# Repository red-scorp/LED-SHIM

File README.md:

# LED-SHIM project

LED-SHIM (mini-HAT), RGB LED array for Raspberry Pi.

Sometimes it's nice to add some shine to your Pi.
This can be achieved with a line or matrix of RGB addressable LEDs.
Welcome to a new shiny world!

## LED-mini20-SHIM

Raspberry Pi mini 40-pin **LED-mini20-SHIM** mini-HAT.

Preview:

[Schematics in PDF format](doc/LED-mini20-SHIM.pdf)

Features:

- locked Pi headers
- data input pin selection
- 18 RGB LEDs organized in a single line
- industry standard WS2812 addressable LEDs
- small board for Pi
- can be used as SHIM (no headers) or HAT (with headers)

Pins Configuration:

|Data Pin |Option 1 |Option 2 |Option 3 |
|---------|---------|---------|---------|
|DI       |GPIO18\* |GPIO10   |GPIO21   |

\*) the pin is connected by default.

CAM files are available.
BoM and PnP files for JLCPCB are available.

## LED-mini35-SHIM

Raspberry Pi mini 40-pin **LED-mini35-SHIM** mini-HAT.

Preview:

[Schematics in PDF format](doc/LED-mini35-SHIM.pdf)

Features:

- locked Pi headers
- data input pin selection
- 12 RGB LEDs organized in a single line
- industry standard WS2812 addressable LEDs
- small board for Pi
- can be used as SHIM (no headers) or HAT (with headers)

Pins Configuration:

|Data Pin |Option 1 |Option 2 |Option 3 |
|---------|---------|---------|---------|
|DI       |GPIO18\* |GPIO10   |GPIO21   |

\*) the pin is connected by default.

CAM files are available.
BoM and PnP files for JLCPCB are available.

## LED-zero20-SHIM

Raspberry Pi zero 40-pin **LED-zero20-SHIM** mini-HAT.

Preview:

[Schematics in PDF format](doc/LED-zero20-SHIM.pdf)

Features:

- locked Pi headers
- data input pin selection
- 144 RGB LEDs organized in a matrix of 18x8
- industry standard WS2812 addressable LEDs
- separate DI and DO headers for extendability
- Pi zero board style
- can be used as SHIM (no headers) or HAT (with headers)

Pins Configuration:

|Data Pin |Option 1 |Option 2 |Option 3 |
|---------|---------|---------|---------|
|DI       |GPIO18\* |GPIO10   |GPIO21   |

\*) the pin is connected by default.

CAM files are available.
BoM and PnP files for JLCPCB are available.

## LED-zero35-SHIM

Raspberry Pi zero 40-pin **LED-zero35-SHIM** mini-HAT.

Preview:

[Schematics in PDF format](LED-zero35-SHIM.pdf)

Features:

- locked Pi headers
- data input pin selection
- 60 RGB LEDs organized in a matrix of 12x5
- industry standard WS2812 addressable LEDs
- separate DI and DO headers for extendability
- Pi zero board style
- can be used as SHIM (no headers) or HAT (with headers)

Pins Configuration:

|Data Pin |Option 1 |Option 2 |Option 3 |
|---------|---------|---------|---------|
|DI       |GPIO18\* |GPIO10   |GPIO21   |

\*) the pin is connected by default.

CAM files are available.
BoM and PnP files for JLCPCB are available.

## LED-plus20-SHIM

Raspberry Pi plus 40-pin **LED-plus20-SHIM** mini-HAT.

Preview:

[Schematics in PDF format](doc/LED-plus20-SHIM.pdf)

Features:

- locked Pi headers
- data input pin selection
- 288 RGB LEDs organized in a matrix of 18x16
- industry standard WS2812 addressable LEDs
- separate DI and DO headers for extendability
- Pi plus board style
- can be used as SHIM (no headers) or HAT (with headers)

Pins Configuration:

|Data Pin |Option 1 |Option 2 |Option 3 |
|---------|---------|---------|---------|
|DI       |GPIO18\* |GPIO10   |GPIO21   |

\*) the pin is connected by default.

CAM files are available.
BoM and PnP files for JLCPCB are available.

## LED-plus35-SHIM

Raspberry Pi plus 40-pin **LED-plus35-SHIM** mini-HAT.

Preview:

[Schematics in PDF format](doc/LED-plus35-SHIM.pdf)

Features:

- locked Pi headers
- data input pin selection
- 120 RGB LEDs organized in a matrix of 12x10
- industry standard WS2812 addressable LEDs
- separate DI and DO headers for extendability
- Pi plus board style
- can be used as SHIM (no headers) or HAT (with headers)

Pins Configuration:

|Data Pin |Option 1 |Option 2 |Option 3 |
|---------|---------|---------|---------|
|DI       |GPIO18\* |GPIO10   |GPIO21   |

\*) the pin is connected by default.

CAM files are available.
BoM and PnP files for JLCPCB are available.

## Links

- [pinout.xyz](https://pinout.xyz/) - a brilliant resource on topic of Pi's pinout and HATs.
- [raspberrypi/hats](https://github.com/raspberrypi/hats) - Pi's HAT specification.

## How to help

Your contributions as code, resources, or finances are welcome! Please contact me directly via email at andriy.golovnya@gmail.com or through my [GitHub profile](https://github.com/red-scorp).

If you'd like to make a financial contribution, you can donate via [PayPal](http://paypal.me/redscorp) or [Ko-Fi](http://ko-fi.com/redscorp). Your support is greatly appreciated.

Thanks in advance!

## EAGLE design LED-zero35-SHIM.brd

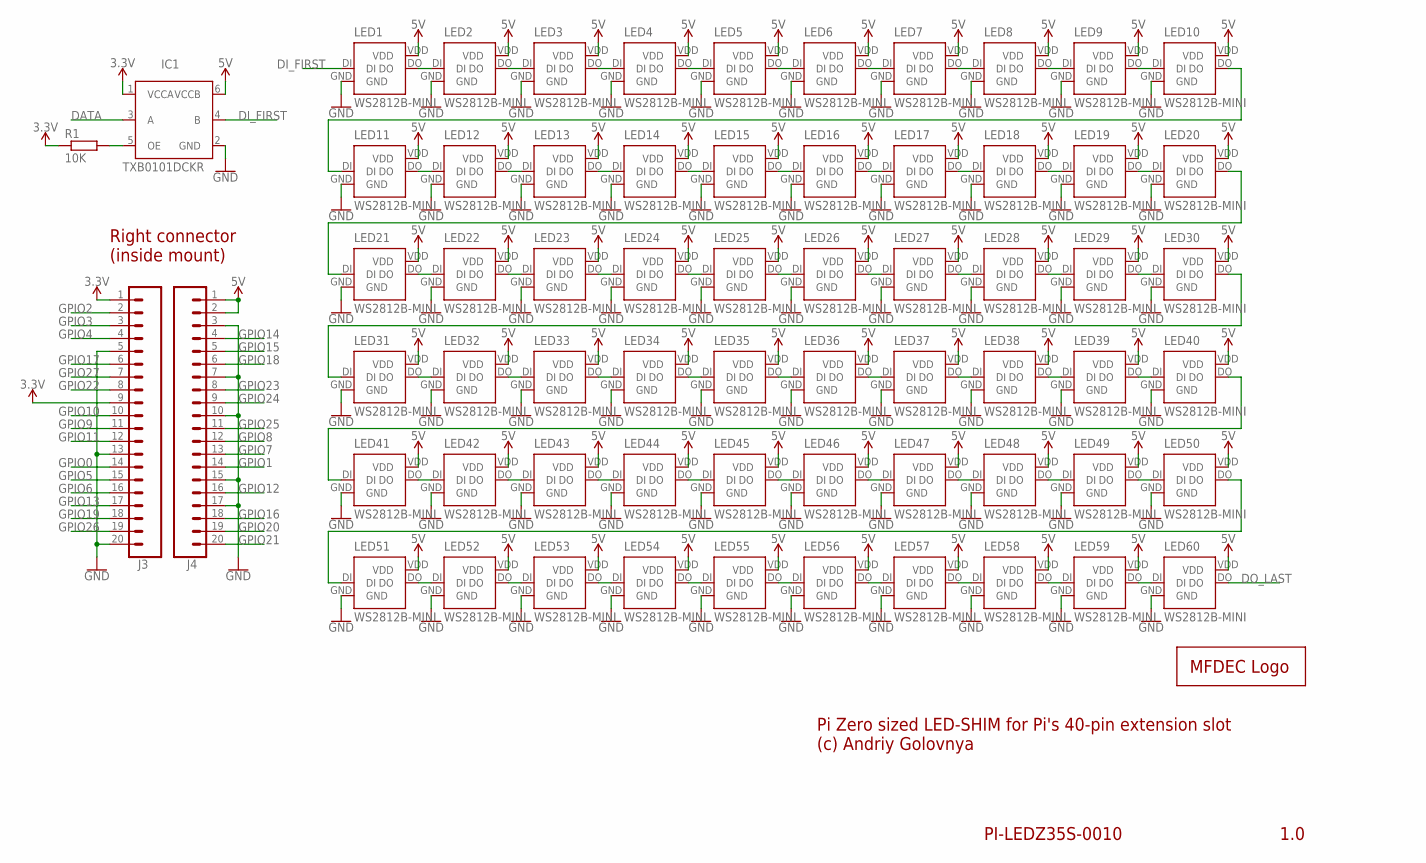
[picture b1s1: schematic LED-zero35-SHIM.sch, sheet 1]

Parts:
IC1: TXB0101DCKR; SOT65P210X110-6N
J3, J4: CONN_20LOCK; 1X20_LOCK
LED1, LED2, LED3, LED4, LED5, LED6, LED7, LED8, LED9, LED10, LED11, LED12, LED13, LED14, LED15, LED16, LED17, LED18, LED19, LED20, LED21, LED22, LED23, LED24, LED25, LED26, LED27, LED28, LED29, LED30, LED31, LED32, LED33, LED34, LED35, LED36, LED37, LED38, LED39, LED40, LED41, LED42, LED43, LED44, LED45, LED46, LED47, LED48, LED49, LED50, LED51, LED52, LED53, LED54, LED55, LED56, LED57, LED58, LED59, LED60: WS2812B-MINI; WS2812X-MINI
LOGO1: MFDECLOGO_L_30MM; MFDEC_L_30MM
R1: 10K; R0402

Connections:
3.3V: IC1.1 (VCCA), J3.1, J3.9, R1.1
5V: IC1.6 (VCCB), J4.1, J4.2, LED1.VDD, LED2.VDD, LED3.VDD, LED4.VDD, LED5.VDD, LED6.VDD, LED7.VDD, LED8.VDD, LED9.VDD, LED10.VDD, LED11.VDD, LED12.VDD, LED13.VDD, LED14.VDD, LED15.VDD, LED16.VDD, LED17.VDD, LED18.VDD, LED19.VDD, LED20.VDD, LED21.VDD, LED22.VDD, LED23.VDD, LED24.VDD, LED25.VDD, LED26.VDD, LED27.VDD, LED28.VDD, LED29.VDD, LED30.VDD, LED31.VDD, LED32.VDD, LED33.VDD, LED34.VDD, LED35.VDD, LED36.VDD, LED37.VDD, LED38.VDD, LED39.VDD, LED40.VDD, LED41.VDD, LED42.VDD, LED43.VDD, LED44.VDD, LED45.VDD, LED46.VDD, LED47.VDD, LED48.VDD, LED49.VDD, LED50.VDD, LED51.VDD, LED52.VDD, LED53.VDD, LED54.VDD, LED55.VDD, LED56.VDD, LED57.VDD, LED58.VDD, LED59.VDD, LED60.VDD; also elsewhere on the board
DATA: IC1.3 (A); also elsewhere on the board
DI_FIRST: IC1.4 (B), LED1.DI; also elsewhere on the board
DO_LAST: LED60.DO; also elsewhere on the board
GND: IC1.2 (GND), J3.5, J3.13, J3.20, J4.3, J4.7, J4.10, J4.15, J4.17, LED1.GND, LED2.GND, LED3.GND, LED4.GND, LED5.GND, LED6.GND, LED7.GND, LED8.GND, LED9.GND, LED10.GND, LED11.GND, LED12.GND, LED13.GND, LED14.GND, LED15.GND, LED16.GND, LED17.GND, LED18.GND, LED19.GND, LED20.GND, LED21.GND, LED22.GND, LED23.GND, LED24.GND, LED25.GND, LED26.GND, LED27.GND, LED28.GND, LED29.GND, LED30.GND, LED31.GND, LED32.GND, LED33.GND, LED34.GND, LED35.GND, LED36.GND, LED37.GND, LED38.GND, LED39.GND, LED40.GND, LED41.GND, LED42.GND, LED43.GND, LED44.GND, LED45.GND, LED46.GND, LED47.GND, LED48.GND, LED49.GND, LED50.GND, LED51.GND, LED52.GND, LED53.GND, LED54.GND, LED55.GND, LED56.GND, LED57.GND, LED58.GND, LED59.GND, LED60.GND; also elsewhere on the board
GPIO0: J3.14
GPIO1: J4.14
GPIO2: J3.2
GPIO3: J3.3
GPIO4: J3.4
GPIO5: J3.15
GPIO6: J3.16
GPIO7: J4.13
GPIO8: J4.12
GPIO9: J3.11
GPIO10: J3.10; also elsewhere on the board
GPIO11: J3.12
GPIO12: J4.16
GPIO13: J3.17
GPIO14: J4.4
GPIO15: J4.5
GPIO16: J4.18
GPIO17: J3.6
GPIO18: J4.6; also elsewhere on the board
GPIO19: J3.18
GPIO20: J4.19
GPIO21: J4.20; also elsewhere on the board
GPIO22: J3.8
GPIO23: J4.8
GPIO24: J4.9
GPIO25: J4.11
GPIO26: J3.19
GPIO27: J3.7
unnamed: LED1.DO, LED2.DI
unnamed: LED2.DO, LED3.DI
unnamed: LED3.DO, LED4.DI
unnamed: LED4.DO, LED5.DI
unnamed: LED5.DO, LED6.DI
unnamed: LED6.DO, LED7.DI
unnamed: LED7.DO, LED8.DI
unnamed: LED8.DO, LED9.DI
unnamed: LED9.DO, LED10.DI
unnamed: LED10.DO, LED11.DI
unnamed: LED11.DO, LED12.DI
unnamed: LED12.DO, LED13.DI
unnamed: LED13.DO, LED14.DI
unnamed: LED14.DO, LED15.DI
unnamed: LED15.DO, LED16.DI
unnamed: LED16.DO, LED17.DI
unnamed: LED17.DO, LED18.DI
unnamed: LED18.DO, LED19.DI
unnamed: LED19.DO, LED20.DI
unnamed: LED20.DO, LED21.DI
unnamed: LED21.DO, LED22.DI
unnamed: LED22.DO, LED23.DI
unnamed: LED23.DO, LED24.DI
unnamed: LED24.DO, LED25.DI
unnamed: LED25.DO, LED26.DI
unnamed: LED26.DO, LED27.DI
unnamed: LED27.DO, LED28.DI
unnamed: LED28.DO, LED29.DI
unnamed: LED29.DO, LED30.DI
unnamed: LED30.DO, LED31.DI
unnamed: LED41.DO, LED42.DI
unnamed: LED31.DO, LED32.DI
unnamed: LED32.DO, LED33.DI
unnamed: LED33.DO, LED34.DI
unnamed: LED34.DO, LED35.DI
unnamed: LED35.DO, LED36.DI
unnamed: LED36.DO, LED37.DI
unnamed: LED37.DO, LED38.DI
unnamed: LED38.DO, LED39.DI
unnamed: LED39.DO, LED40.DI
unnamed: LED40.DO, LED41.DI
unnamed: LED42.DO, LED43.DI
unnamed: LED43.DO, LED44.DI
unnamed: LED44.DO, LED45.DI
unnamed: LED45.DO, LED46.DI
unnamed: LED46.DO, LED47.DI
unnamed: LED47.DO, LED48.DI
unnamed: LED48.DO, LED49.DI
unnamed: LED49.DO, LED50.DI
unnamed: LED50.DO, LED51.DI
unnamed: LED51.DO, LED52.DI
unnamed: LED52.DO, LED53.DI
unnamed: LED53.DO, LED54.DI
unnamed: LED54.DO, LED55.DI
unnamed: LED55.DO, LED56.DI
unnamed: LED56.DO, LED57.DI
unnamed: LED57.DO, LED58.DI
unnamed: LED58.DO, LED59.DI
unnamed: LED59.DO, LED60.DI
unnamed: IC1.5 (OE), R1.2

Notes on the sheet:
1.0
PI-LEDZ35S-0010
Pi Zero sized LED-SHIM for Pi's 40-pin extension slot (c) Andriy Golovnya
Right connector (inside mount)

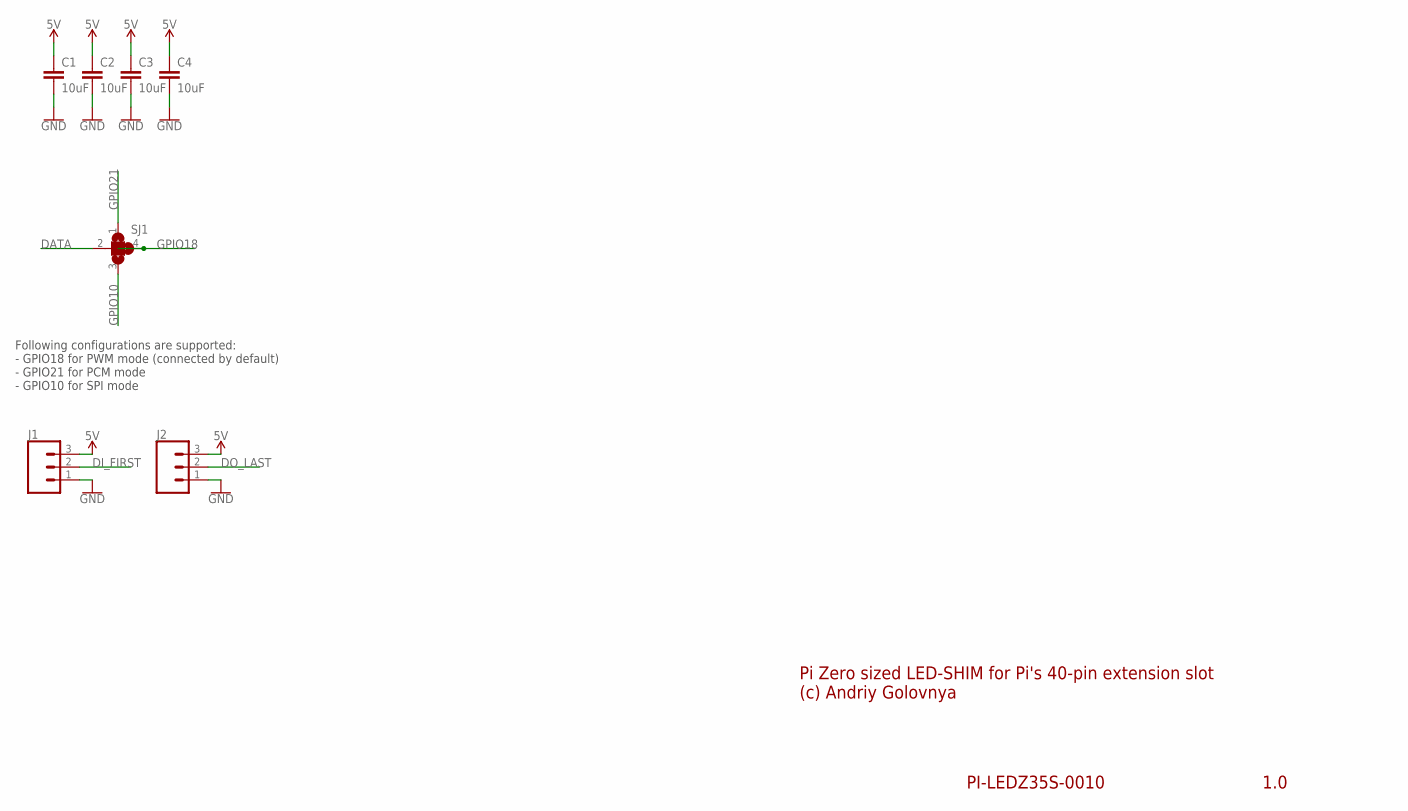
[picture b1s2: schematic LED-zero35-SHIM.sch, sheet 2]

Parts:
C1, C2, C3, C4: 10uF; C0805
J1, J2: CONN_03; 1X03
SJ1: SJ3; SJ_3

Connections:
5V: C1.1, C2.1, C3.1, C4.1, J1.3, J2.3; also elsewhere on the board
DATA: SJ1.2; also elsewhere on the board
DI_FIRST: J1.2; also elsewhere on the board
DO_LAST: J2.2; also elsewhere on the board
GND: C1.2, C2.2, C3.2, C4.2, J1.1, J2.1; also elsewhere on the board
GPIO10: SJ1.3; also elsewhere on the board
GPIO18: SJ1.4; also elsewhere on the board
GPIO21: SJ1.1; also elsewhere on the board

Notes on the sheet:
1.0
PI-LEDZ35S-0010
Pi Zero sized LED-SHIM for Pi's 40-pin extension slot (c) Andriy Golovnya
Following configurations are supported: - GPIO18 for PWM mode (connected by default) - GPIO21 for PCM mode - GPIO10 for SPI mode

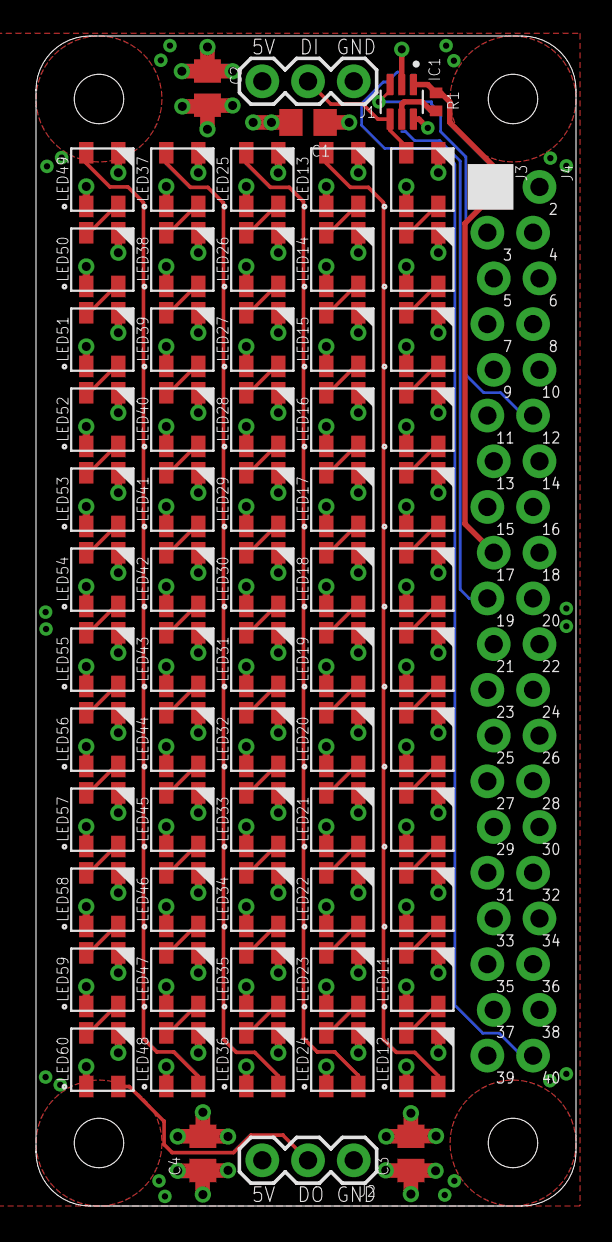
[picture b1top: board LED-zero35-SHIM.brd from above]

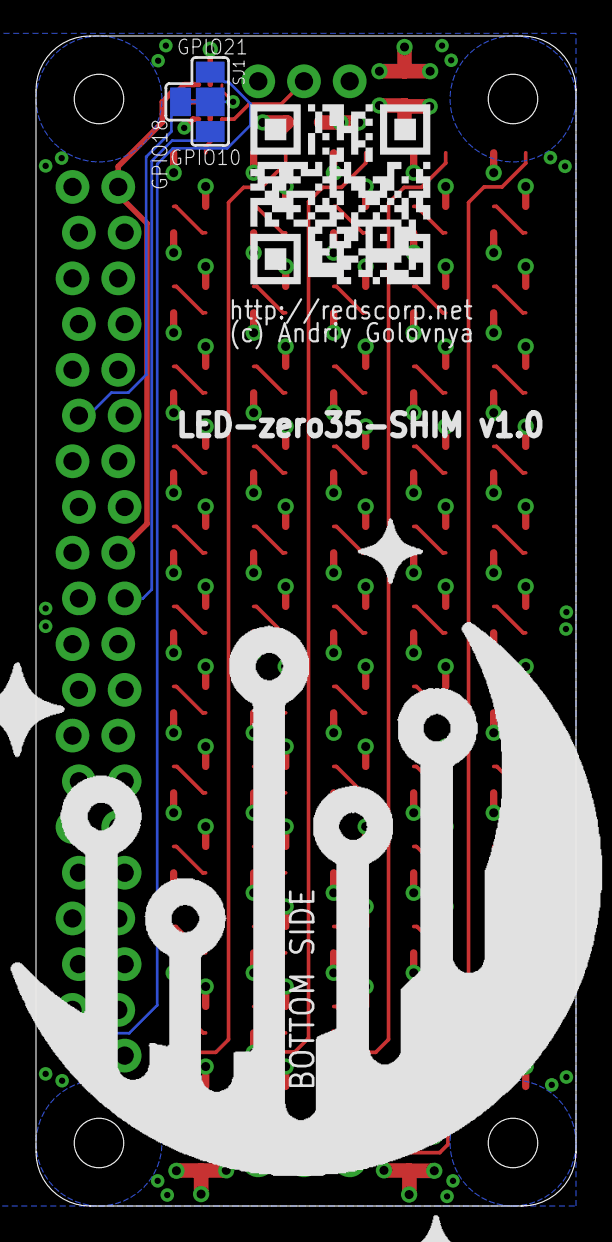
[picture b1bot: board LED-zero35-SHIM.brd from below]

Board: 4 copper layers, 30.0 x 65.0 mm, 73 parts (3 on the bottom side), 69 nets.

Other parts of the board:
LOGO3: RSNURL_QR_10MM

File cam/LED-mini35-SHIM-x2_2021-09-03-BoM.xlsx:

Qty | Designator | Footprint | Comment | LCSC Part #
2 | R1, R2 | 0402 | 10K | C25744
2 | C1, C2, C3, C4 | 0805 | 10uF | C15850
2 | IC1, IC2 | SC-70-6 | TXB0101DCKR | C324081
12 | LED1, LED2, LED3, LED4, LED5, LED6, LED7, LED8, LED9, LED10, LED11, LED12, LED1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 | LED-4_3535 | WS2812B-MINI | C114583

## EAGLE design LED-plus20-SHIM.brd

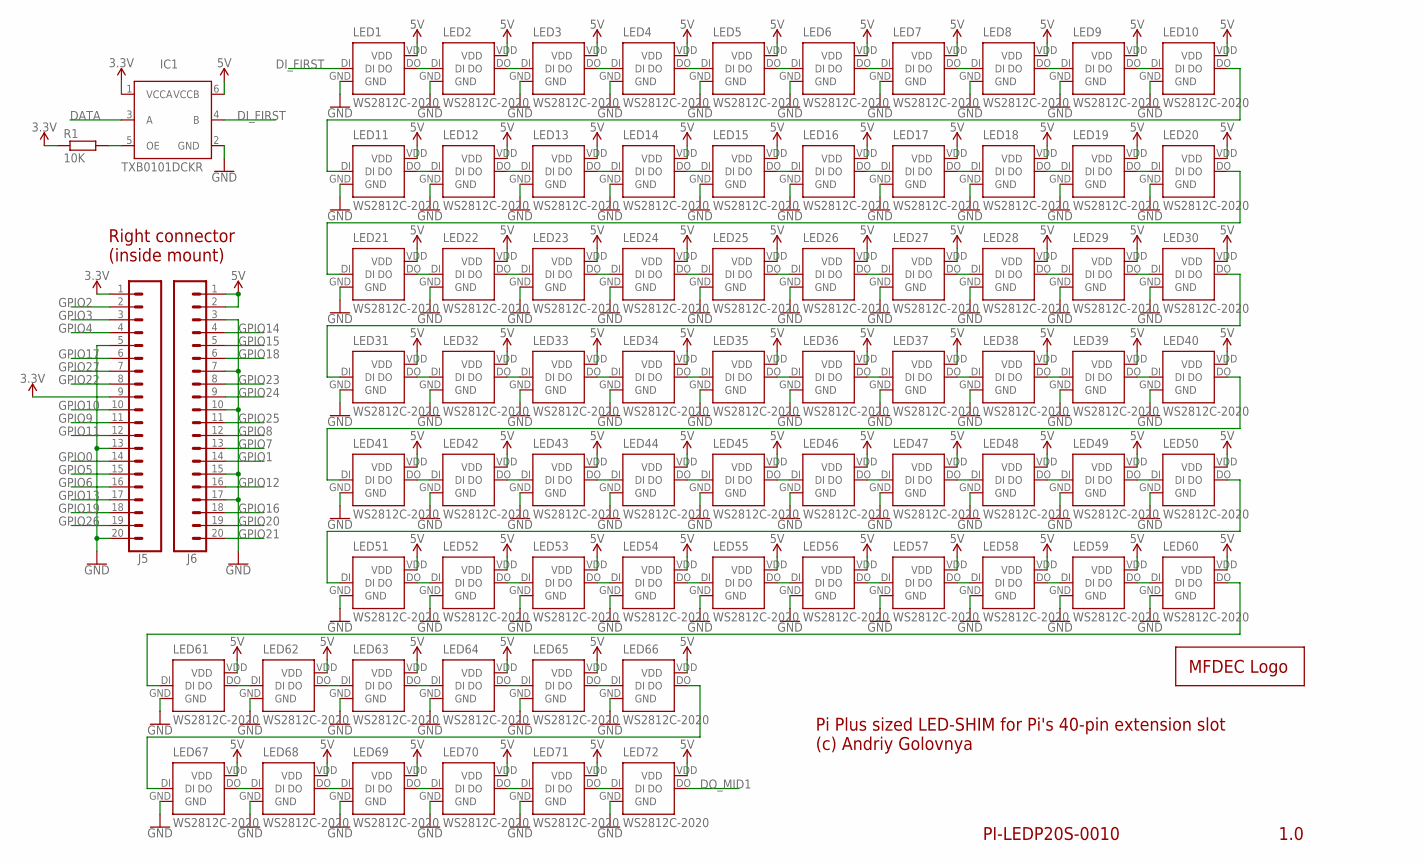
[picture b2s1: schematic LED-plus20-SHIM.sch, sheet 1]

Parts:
IC1: TXB0101DCKR; SOT65P210X110-6N
J5, J6: CONN_20LOCK; 1X20_LOCK
LED1, LED2, LED3, LED4, LED5, LED6, LED7, LED8, LED9, LED10, LED11, LED12, LED13, LED14, LED15, LED16, LED17, LED18, LED19, LED20, LED21, LED22, LED23, LED24, LED25, LED26, LED27, LED28, LED29, LED30, LED31, LED32, LED33, LED34, LED35, LED36, LED37, LED38, LED39, LED40, LED41, LED42, LED43, LED44, LED45, LED46, LED47, LED48, LED49, LED50, LED51, LED52, LED53, LED54, LED55, LED56, LED57, LED58, LED59, LED60, LED61, LED62, LED63, LED64, LED65, LED66, LED67, LED68, LED69, LED70, LED71, LED72: WS2812C-2020; WS2812X-2020
LOGO1: MFDECLOGO_L_40MM; MFDEC_L_40MM
R1: 10K; R0402

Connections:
3.3V: IC1.1 (VCCA), J5.1, J5.9, R1.1
5V: IC1.6 (VCCB), J6.1, J6.2, LED1.VDD, LED2.VDD, LED3.VDD, LED4.VDD, LED5.VDD, LED6.VDD, LED7.VDD, LED8.VDD, LED9.VDD, LED10.VDD, LED11.VDD, LED12.VDD, LED13.VDD, LED14.VDD, LED15.VDD, LED16.VDD, LED17.VDD, LED18.VDD, LED19.VDD, LED20.VDD, LED21.VDD, LED22.VDD, LED23.VDD, LED24.VDD, LED25.VDD, LED26.VDD, LED27.VDD, LED28.VDD, LED29.VDD, LED30.VDD, LED31.VDD, LED32.VDD, LED33.VDD, LED34.VDD, LED35.VDD, LED36.VDD, LED37.VDD, LED38.VDD, LED39.VDD, LED40.VDD, LED41.VDD, LED42.VDD, LED43.VDD, LED44.VDD, LED45.VDD, LED46.VDD, LED47.VDD, LED48.VDD, LED49.VDD, LED50.VDD, LED51.VDD, LED52.VDD, LED53.VDD, LED54.VDD, LED55.VDD, LED56.VDD, LED57.VDD, LED58.VDD, LED59.VDD, LED60.VDD, LED61.VDD, LED62.VDD, LED63.VDD, LED64.VDD, LED65.VDD, LED66.VDD, LED67.VDD, LED68.VDD, LED69.VDD, LED70.VDD, LED71.VDD, LED72.VDD; also elsewhere on the board
DATA: IC1.3 (A); also elsewhere on the board
DI_FIRST: IC1.4 (B), LED1.DI; also elsewhere on the board
DO_MID1: LED72.DO; also elsewhere on the board
GND: IC1.2 (GND), J5.5, J5.13, J5.20, J6.3, J6.7, J6.10, J6.15, J6.17, LED1.GND, LED2.GND, LED3.GND, LED4.GND, LED5.GND, LED6.GND, LED7.GND, LED8.GND, LED9.GND, LED10.GND, LED11.GND, LED12.GND, LED13.GND, LED14.GND, LED15.GND, LED16.GND, LED17.GND, LED18.GND, LED19.GND, LED20.GND, LED21.GND, LED22.GND, LED23.GND, LED24.GND, LED25.GND, LED26.GND, LED27.GND, LED28.GND, LED29.GND, LED30.GND, LED31.GND, LED32.GND, LED33.GND, LED34.GND, LED35.GND, LED36.GND, LED37.GND, LED38.GND, LED39.GND, LED40.GND, LED41.GND, LED42.GND, LED43.GND, LED44.GND, LED45.GND, LED46.GND, LED47.GND, LED48.GND, LED49.GND, LED50.GND, LED51.GND, LED52.GND, LED53.GND, LED54.GND, LED55.GND, LED56.GND, LED57.GND, LED58.GND, LED59.GND, LED60.GND, LED61.GND, LED62.GND, LED63.GND, LED64.GND, LED65.GND, LED66.GND, LED67.GND, LED68.GND, LED69.GND, LED70.GND, LED71.GND, LED72.GND; also elsewhere on the board
GPIO0: J5.14
GPIO1: J6.14
GPIO2: J5.2
GPIO3: J5.3
GPIO4: J5.4
GPIO5: J5.15
GPIO6: J5.16
GPIO7: J6.13
GPIO8: J6.12
GPIO9: J5.11
GPIO10: J5.10; also elsewhere on the board
GPIO11: J5.12
GPIO12: J6.16
GPIO13: J5.17
GPIO14: J6.4
GPIO15: J6.5
GPIO16: J6.18
GPIO17: J5.6
GPIO18: J6.6; also elsewhere on the board
GPIO19: J5.18
GPIO20: J6.19
GPIO21: J6.20; also elsewhere on the board
GPIO22: J5.8
GPIO23: J6.8
GPIO24: J6.9
GPIO25: J6.11
GPIO26: J5.19
GPIO27: J5.7
unnamed: LED1.DO, LED2.DI
unnamed: LED2.DO, LED3.DI
unnamed: LED3.DO, LED4.DI
unnamed: LED4.DO, LED5.DI
unnamed: LED5.DO, LED6.DI
unnamed: LED6.DO, LED7.DI
unnamed: LED7.DO, LED8.DI
unnamed: LED8.DO, LED9.DI
unnamed: LED9.DO, LED10.DI
unnamed: LED10.DO, LED11.DI
unnamed: LED11.DO, LED12.DI
unnamed: LED12.DO, LED13.DI
unnamed: LED13.DO, LED14.DI
unnamed: LED14.DO, LED15.DI
unnamed: LED15.DO, LED16.DI
unnamed: LED16.DO, LED17.DI
unnamed: LED17.DO, LED18.DI
unnamed: LED18.DO, LED19.DI
unnamed: LED19.DO, LED20.DI
unnamed: LED20.DO, LED21.DI
unnamed: LED21.DO, LED22.DI
unnamed: LED22.DO, LED23.DI
unnamed: LED23.DO, LED24.DI
unnamed: LED24.DO, LED25.DI
unnamed: LED25.DO, LED26.DI
unnamed: LED26.DO, LED27.DI
unnamed: LED27.DO, LED28.DI
unnamed: LED28.DO, LED29.DI
unnamed: LED29.DO, LED30.DI
unnamed: LED30.DO, LED31.DI
unnamed: LED31.DO, LED32.DI
unnamed: LED32.DO, LED33.DI
unnamed: LED33.DO, LED34.DI
unnamed: LED34.DO, LED35.DI
unnamed: LED35.DO, LED36.DI
unnamed: LED36.DO, LED37.DI
unnamed: LED37.DO, LED38.DI
unnamed: LED38.DO, LED39.DI
unnamed: LED39.DO, LED40.DI
unnamed: LED40.DO, LED41.DI
unnamed: LED41.DO, LED42.DI
unnamed: LED42.DO, LED43.DI
unnamed: LED43.DO, LED44.DI
unnamed: LED44.DO, LED45.DI
unnamed: LED45.DO, LED46.DI
unnamed: LED46.DO, LED47.DI
unnamed: LED47.DO, LED48.DI
unnamed: LED48.DO, LED49.DI
unnamed: LED49.DO, LED50.DI
unnamed: LED50.DO, LED51.DI
unnamed: LED51.DO, LED52.DI
unnamed: LED52.DO, LED53.DI
unnamed: LED53.DO, LED54.DI
unnamed: LED54.DO, LED55.DI
unnamed: LED55.DO, LED56.DI
unnamed: LED56.DO, LED57.DI
unnamed: LED57.DO, LED58.DI
unnamed: LED58.DO, LED59.DI
unnamed: LED59.DO, LED60.DI
unnamed: LED60.DO, LED61.DI
unnamed: LED61.DO, LED62.DI
unnamed: LED62.DO, LED63.DI
unnamed: LED63.DO, LED64.DI
unnamed: LED64.DO, LED65.DI
unnamed: LED65.DO, LED66.DI
unnamed: LED66.DO, LED67.DI
unnamed: LED67.DO, LED68.DI
unnamed: LED68.DO, LED69.DI
unnamed: LED69.DO, LED70.DI
unnamed: LED70.DO, LED71.DI
unnamed: LED71.DO, LED72.DI
unnamed: IC1.5 (OE), R1.2

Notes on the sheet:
1.0
PI-LEDP20S-0010
Pi Plus sized LED-SHIM for Pi's 40-pin extension slot (c) Andriy Golovnya
Right connector (inside mount)

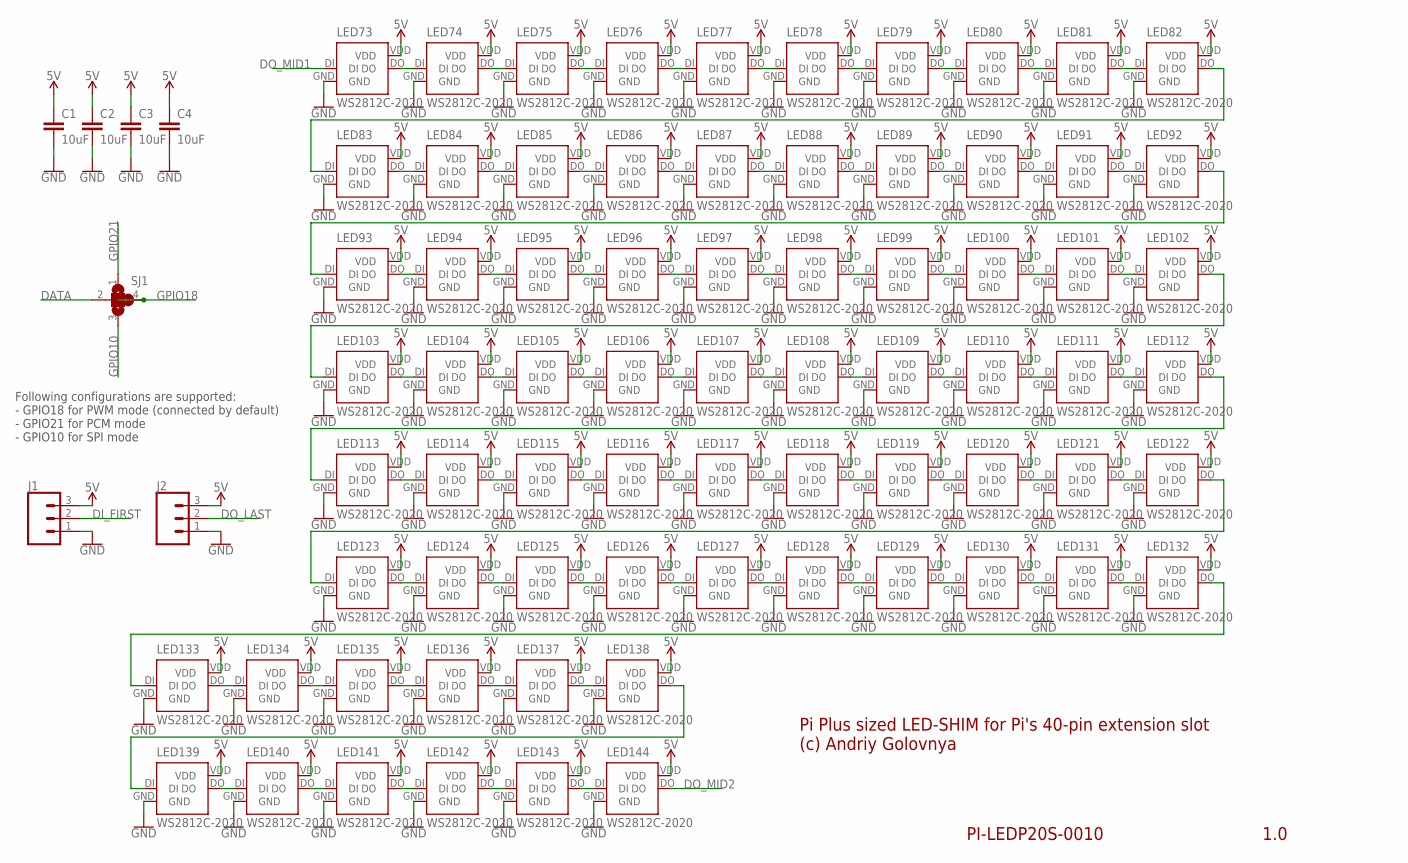
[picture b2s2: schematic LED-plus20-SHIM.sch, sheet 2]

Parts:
C1, C2, C3, C4: 10uF; C0805
J1, J2: CONN_03; 1X03
LED73, LED74, LED75, LED76, LED77, LED78, LED79, LED80, LED81, LED82, LED83, LED84, LED85, LED86, LED87, LED88, LED89, LED90, LED91, LED92, LED93, LED94, LED95, LED96, LED97, LED98, LED99, LED100, LED101, LED102, LED103, LED104, LED105, LED106, LED107, LED108, LED109, LED110, LED111, LED112, LED113, LED114, LED115, LED116, LED117, LED118, LED119, LED120, LED121, LED122, LED123, LED124, LED125, LED126, LED127, LED128, LED129, LED130, LED131, LED132, LED133, LED134, LED135, LED136, LED137, LED138, LED139, LED140, LED141, LED142, LED143, LED144: WS2812C-2020; WS2812X-2020
SJ1: SJ3; SJ_3

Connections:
5V: C1.1, C2.1, C3.1, C4.1, J1.3, J2.3, LED73.VDD, LED74.VDD, LED75.VDD, LED76.VDD, LED77.VDD, LED78.VDD, LED79.VDD, LED80.VDD, LED81.VDD, LED82.VDD, LED83.VDD, LED84.VDD, LED85.VDD, LED86.VDD, LED87.VDD, LED88.VDD, LED89.VDD, LED90.VDD, LED91.VDD, LED92.VDD, LED93.VDD, LED94.VDD, LED95.VDD, LED96.VDD, LED97.VDD, LED98.VDD, LED99.VDD, LED100.VDD, LED101.VDD, LED102.VDD, LED103.VDD, LED104.VDD, LED105.VDD, LED106.VDD, LED107.VDD, LED108.VDD, LED109.VDD, LED110.VDD, LED111.VDD, LED112.VDD, LED113.VDD, LED114.VDD, LED115.VDD, LED116.VDD, LED117.VDD, LED118.VDD, LED119.VDD, LED120.VDD, LED121.VDD, LED122.VDD, LED123.VDD, LED124.VDD, LED125.VDD, LED126.VDD, LED127.VDD, LED128.VDD, LED129.VDD, LED130.VDD, LED131.VDD, LED132.VDD, LED133.VDD, LED134.VDD, LED135.VDD, LED136.VDD, LED137.VDD, LED138.VDD, LED139.VDD, LED140.VDD, LED141.VDD, LED142.VDD, LED143.VDD, LED144.VDD; also elsewhere on the board
DATA: SJ1.2; also elsewhere on the board
DI_FIRST: J1.2; also elsewhere on the board
DO_LAST: J2.2; also elsewhere on the board
DO_MID1: LED73.DI; also elsewhere on the board
DO_MID2: LED144.DO; also elsewhere on the board
GND: C1.2, C2.2, C3.2, C4.2, J1.1, J2.1, LED73.GND, LED74.GND, LED75.GND, LED76.GND, LED77.GND, LED78.GND, LED79.GND, LED80.GND, LED81.GND, LED82.GND, LED83.GND, LED84.GND, LED85.GND, LED86.GND, LED87.GND, LED88.GND, LED89.GND, LED90.GND, LED91.GND, LED92.GND, LED93.GND, LED94.GND, LED95.GND, LED96.GND, LED97.GND, LED98.GND, LED99.GND, LED100.GND, LED101.GND, LED102.GND, LED103.GND, LED104.GND, LED105.GND, LED106.GND, LED107.GND, LED108.GND, LED109.GND, LED110.GND, LED111.GND, LED112.GND, LED113.GND, LED114.GND, LED115.GND, LED116.GND, LED117.GND, LED118.GND, LED119.GND, LED120.GND, LED121.GND, LED122.GND, LED123.GND, LED124.GND, LED125.GND, LED126.GND, LED127.GND, LED128.GND, LED129.GND, LED130.GND, LED131.GND, LED132.GND, LED133.GND, LED134.GND, LED135.GND, LED136.GND, LED137.GND, LED138.GND, LED139.GND, LED140.GND, LED141.GND, LED142.GND, LED143.GND, LED144.GND; also elsewhere on the board
GPIO10: SJ1.3; also elsewhere on the board
GPIO18: SJ1.4; also elsewhere on the board
GPIO21: SJ1.1; also elsewhere on the board
unnamed: LED73.DO, LED74.DI
unnamed: LED74.DO, LED75.DI
unnamed: LED75.DO, LED76.DI
unnamed: LED76.DO, LED77.DI
unnamed: LED77.DO, LED78.DI
unnamed: LED78.DO, LED79.DI
unnamed: LED79.DO, LED80.DI
unnamed: LED80.DO, LED81.DI
unnamed: LED81.DO, LED82.DI
unnamed: LED82.DO, LED83.DI
unnamed: LED83.DO, LED84.DI
unnamed: LED84.DO, LED85.DI
unnamed: LED85.DO, LED86.DI
unnamed: LED86.DO, LED87.DI
unnamed: LED87.DO, LED88.DI
unnamed: LED88.DO, LED89.DI
unnamed: LED89.DO, LED90.DI
unnamed: LED90.DO, LED91.DI
unnamed: LED91.DO, LED92.DI
unnamed: LED92.DO, LED93.DI
unnamed: LED93.DO, LED94.DI
unnamed: LED94.DO, LED95.DI
unnamed: LED95.DO, LED96.DI
unnamed: LED96.DO, LED97.DI
unnamed: LED97.DO, LED98.DI
unnamed: LED98.DO, LED99.DI
unnamed: LED99.DO, LED100.DI
unnamed: LED100.DO, LED101.DI
unnamed: LED101.DO, LED102.DI
unnamed: LED102.DO, LED103.DI
unnamed: LED103.DO, LED104.DI
unnamed: LED104.DO, LED105.DI
unnamed: LED105.DO, LED106.DI
unnamed: LED106.DO, LED107.DI
unnamed: LED107.DO, LED108.DI
unnamed: LED108.DO, LED109.DI
unnamed: LED109.DO, LED110.DI
unnamed: LED110.DO, LED111.DI
unnamed: LED111.DO, LED112.DI
unnamed: LED112.DO, LED113.DI
unnamed: LED113.DO, LED114.DI
unnamed: LED114.DO, LED115.DI
unnamed: LED115.DO, LED116.DI
unnamed: LED116.DO, LED117.DI
unnamed: LED117.DO, LED118.DI
unnamed: LED118.DO, LED119.DI
unnamed: LED119.DO, LED120.DI
unnamed: LED120.DO, LED121.DI
unnamed: LED121.DO, LED122.DI
unnamed: LED122.DO, LED123.DI
unnamed: LED123.DO, LED124.DI
unnamed: LED124.DO, LED125.DI
unnamed: LED125.DO, LED126.DI
unnamed: LED126.DO, LED127.DI
unnamed: LED127.DO, LED128.DI
unnamed: LED128.DO, LED129.DI
unnamed: LED129.DO, LED130.DI
unnamed: LED130.DO, LED131.DI
unnamed: LED131.DO, LED132.DI
unnamed: LED132.DO, LED133.DI
unnamed: LED133.DO, LED134.DI
unnamed: LED134.DO, LED135.DI
unnamed: LED135.DO, LED136.DI
unnamed: LED136.DO, LED137.DI
unnamed: LED137.DO, LED138.DI
unnamed: LED138.DO, LED139.DI
unnamed: LED139.DO, LED140.DI
unnamed: LED140.DO, LED141.DI
unnamed: LED141.DO, LED142.DI
unnamed: LED142.DO, LED143.DI
unnamed: LED143.DO, LED144.DI

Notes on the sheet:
1.0
PI-LEDP20S-0010
Pi Plus sized LED-SHIM for Pi's 40-pin extension slot (c) Andriy Golovnya
Following configurations are supported: - GPIO18 for PWM mode (connected by default) - GPIO21 for PCM mode - GPIO10 for SPI mode

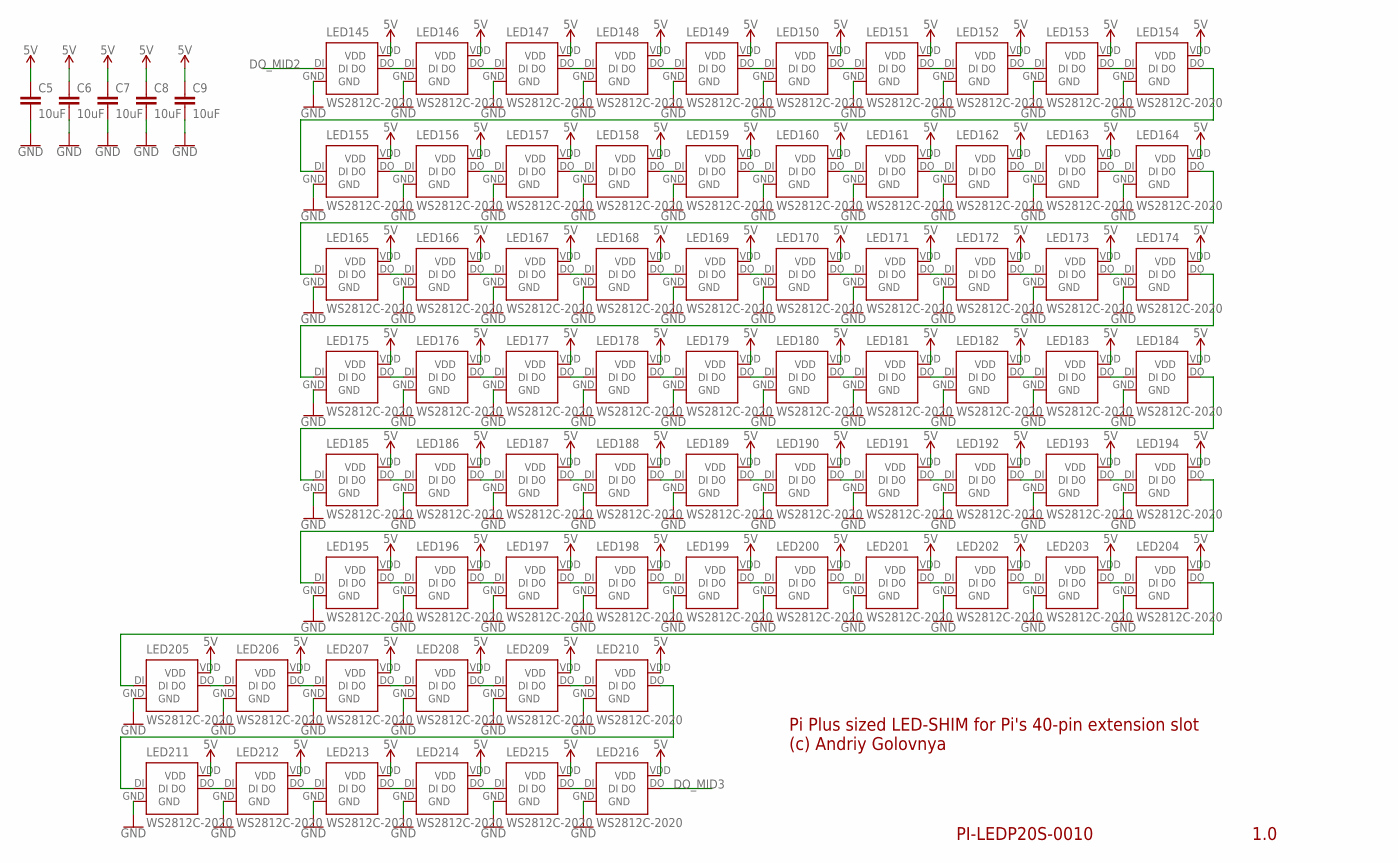
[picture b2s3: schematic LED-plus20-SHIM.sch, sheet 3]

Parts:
C5, C6, C7, C8, C9: 10uF; C0805
LED145, LED146, LED147, LED148, LED149, LED150, LED151, LED152, LED153, LED154, LED155, LED156, LED157, LED158, LED159, LED160, LED161, LED162, LED163, LED164, LED165, LED166, LED167, LED168, LED169, LED170, LED171, LED172, LED173, LED174, LED175, LED176, LED177, LED178, LED179, LED180, LED181, LED182, LED183, LED184, LED185, LED186, LED187, LED188, LED189, LED190, LED191, LED192, LED193, LED194, LED195, LED196, LED197, LED198, LED199, LED200, LED201, LED202, LED203, LED204, LED205, LED206, LED207, LED208, LED209, LED210, LED211, LED212, LED213, LED214, LED215, LED216: WS2812C-2020; WS2812X-2020

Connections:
5V: C5.1, C6.1, C7.1, C8.1, C9.1, LED145.VDD, LED146.VDD, LED147.VDD, LED148.VDD, LED149.VDD, LED150.VDD, LED151.VDD, LED152.VDD, LED153.VDD, LED154.VDD, LED155.VDD, LED156.VDD, LED157.VDD, LED158.VDD, LED159.VDD, LED160.VDD, LED161.VDD, LED162.VDD, LED163.VDD, LED164.VDD, LED165.VDD, LED166.VDD, LED167.VDD, LED168.VDD, LED169.VDD, LED170.VDD, LED171.VDD, LED172.VDD, LED173.VDD, LED174.VDD, LED175.VDD, LED176.VDD, LED177.VDD, LED178.VDD, LED179.VDD, LED180.VDD, LED181.VDD, LED182.VDD, LED183.VDD, LED184.VDD, LED185.VDD, LED186.VDD, LED187.VDD, LED188.VDD, LED189.VDD, LED190.VDD, LED191.VDD, LED192.VDD, LED193.VDD, LED194.VDD, LED195.VDD, LED196.VDD, LED197.VDD, LED198.VDD, LED199.VDD, LED200.VDD, LED201.VDD, LED202.VDD, LED203.VDD, LED204.VDD, LED205.VDD, LED206.VDD, LED207.VDD, LED208.VDD, LED209.VDD, LED210.VDD, LED211.VDD, LED212.VDD, LED213.VDD, LED214.VDD, LED215.VDD, LED216.VDD; also elsewhere on the board
DO_MID2: LED145.DI; also elsewhere on the board
DO_MID3: LED216.DO; also elsewhere on the board
GND: C5.2, C6.2, C7.2, C8.2, C9.2, LED145.GND, LED146.GND, LED147.GND, LED148.GND, LED149.GND, LED150.GND, LED151.GND, LED152.GND, LED153.GND, LED154.GND, LED155.GND, LED156.GND, LED157.GND, LED158.GND, LED159.GND, LED160.GND, LED161.GND, LED162.GND, LED163.GND, LED164.GND, LED165.GND, LED166.GND, LED167.GND, LED168.GND, LED169.GND, LED170.GND, LED171.GND, LED172.GND, LED173.GND, LED174.GND, LED175.GND, LED176.GND, LED177.GND, LED178.GND, LED179.GND, LED180.GND, LED181.GND, LED182.GND, LED183.GND, LED184.GND, LED185.GND, LED186.GND, LED187.GND, LED188.GND, LED189.GND, LED190.GND, LED191.GND, LED192.GND, LED193.GND, LED194.GND, LED195.GND, LED196.GND, LED197.GND, LED198.GND, LED199.GND, LED200.GND, LED201.GND, LED202.GND, LED203.GND, LED204.GND, LED205.GND, LED206.GND, LED207.GND, LED208.GND, LED209.GND, LED210.GND, LED211.GND, LED212.GND, LED213.GND, LED214.GND, LED215.GND, LED216.GND; also elsewhere on the board
unnamed: LED145.DO, LED146.DI
unnamed: LED146.DO, LED147.DI
unnamed: LED147.DO, LED148.DI
unnamed: LED148.DO, LED149.DI
unnamed: LED149.DO, LED150.DI
unnamed: LED150.DO, LED151.DI
unnamed: LED151.DO, LED152.DI
unnamed: LED152.DO, LED153.DI
unnamed: LED153.DO, LED154.DI
unnamed: LED154.DO, LED155.DI
unnamed: LED155.DO, LED156.DI
unnamed: LED156.DO, LED157.DI
unnamed: LED157.DO, LED158.DI
unnamed: LED158.DO, LED159.DI
unnamed: LED159.DO, LED160.DI
unnamed: LED160.DO, LED161.DI
unnamed: LED161.DO, LED162.DI
unnamed: LED162.DO, LED163.DI
unnamed: LED163.DO, LED164.DI
unnamed: LED164.DO, LED165.DI
unnamed: LED165.DO, LED166.DI
unnamed: LED166.DO, LED167.DI
unnamed: LED167.DO, LED168.DI
unnamed: LED168.DO, LED169.DI
unnamed: LED169.DO, LED170.DI
unnamed: LED170.DO, LED171.DI
unnamed: LED171.DO, LED172.DI
unnamed: LED172.DO, LED173.DI
unnamed: LED173.DO, LED174.DI
unnamed: LED174.DO, LED175.DI
unnamed: LED175.DO, LED176.DI
unnamed: LED176.DO, LED177.DI
unnamed: LED177.DO, LED178.DI
unnamed: LED178.DO, LED179.DI
unnamed: LED179.DO, LED180.DI
unnamed: LED180.DO, LED181.DI
unnamed: LED181.DO, LED182.DI
unnamed: LED182.DO, LED183.DI
unnamed: LED183.DO, LED184.DI
unnamed: LED184.DO, LED185.DI
unnamed: LED185.DO, LED186.DI
unnamed: LED186.DO, LED187.DI
unnamed: LED187.DO, LED188.DI
unnamed: LED188.DO, LED189.DI
unnamed: LED189.DO, LED190.DI
unnamed: LED190.DO, LED191.DI
unnamed: LED191.DO, LED192.DI
unnamed: LED192.DO, LED193.DI
unnamed: LED193.DO, LED194.DI
unnamed: LED194.DO, LED195.DI
unnamed: LED195.DO, LED196.DI
unnamed: LED196.DO, LED197.DI
unnamed: LED197.DO, LED198.DI
unnamed: LED198.DO, LED199.DI
unnamed: LED199.DO, LED200.DI
unnamed: LED200.DO, LED201.DI
unnamed: LED201.DO, LED202.DI
unnamed: LED202.DO, LED203.DI
unnamed: LED203.DO, LED204.DI
unnamed: LED204.DO, LED205.DI
unnamed: LED205.DO, LED206.DI
unnamed: LED206.DO, LED207.DI
unnamed: LED207.DO, LED208.DI
unnamed: LED208.DO, LED209.DI
unnamed: LED209.DO, LED210.DI
unnamed: LED210.DO, LED211.DI
unnamed: LED211.DO, LED212.DI
unnamed: LED212.DO, LED213.DI
unnamed: LED213.DO, LED214.DI
unnamed: LED214.DO, LED215.DI
unnamed: LED215.DO, LED216.DI

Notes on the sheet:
1.0
PI-LEDP20S-0010
Pi Plus sized LED-SHIM for Pi's 40-pin extension slot (c) Andriy Golovnya

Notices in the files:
parts and their libraries:
SparkFun-Connectors: Licensing: Creative Commons ShareAlike 4.0 International - https://creativecommons.org/licenses/by-sa/4.0
